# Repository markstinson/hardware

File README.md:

Internal OPL3 ISA 8 bits

version 1.0

With problems still unidentified. The schematic is based on texelec board Resound v1.1:

https://texelec.com/product/resound-opl3-4-channel-opl3-sound-card-8-bit-isa/

Symptoms:

The first start is always correct, it works and you can hear it perfectly, clear FM OPL3 sound ... but after approximately 2 minutes, it stops working. Normally a sleep period without connecting makes it work again, but there have been cases in which it stops working forever... it seems some kind of overload.

The ICs or components do not look hot, and the voltage tracks are not larger than the rest of the signals, this could be an error, however the width of the same should be sufficient for the mA demand of the ICs (I think) .

Another theory is that I do not use electrolytic 10uF capacitors as in the original design, they are 10uF without polarity, but in principle I think that should not affect the operation.

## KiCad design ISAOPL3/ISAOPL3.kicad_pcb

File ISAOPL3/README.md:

Internal OPL3 ISA 8 bits

version 1.0

With problems still unidentified. The schematic is based on texelec board Resound v1.1:

https://texelec.com/product/resound-opl3-4-channel-opl3-sound-card-8-bit-isa/

Symptoms:

The first start is always correct, it works and you can hear it perfectly, clear FM OPL3 sound ... but after approximately 2 minutes, it stops working. Normally a sleep period without connecting makes it work again, but there have been cases in which it stops working forever...  (that should be because component 74245 was not TTL, I've already put a TTL in it, now it always works after a rest period):

https://youtu.be/4GyFgOpV200

The ICs or components do not look hot, and the voltage tracks are not larger than the rest of the signals, this could be an error, however the width of the same should be sufficient for the mA demand of the ICs (I think) .

Another theory is that I do not use electrolytic 10uF capacitors as in the original design, they are 10uF without polarity, but in principle I think that should not affect the operation.

Is the width of the tracks? Is the position of the components? Is it the quality or type of components? Those're the questions.

Issue found:

The problem is in the 1uF WIMA capacitors. If after losing the sound I uncharge them with my finger, it works again!

There is a slight difference with the design of the Resound OPL, I have put the 1uJ63 on it and they use the 1uM63. I will try to determine that it is not any other design problem, in principle by replacing them with 1uF MLCCs.

Fix: 

Specifically the primary 1uF capacitors were left charged, I have solved this by adding a couple of resistors, I will post a demo video soon...

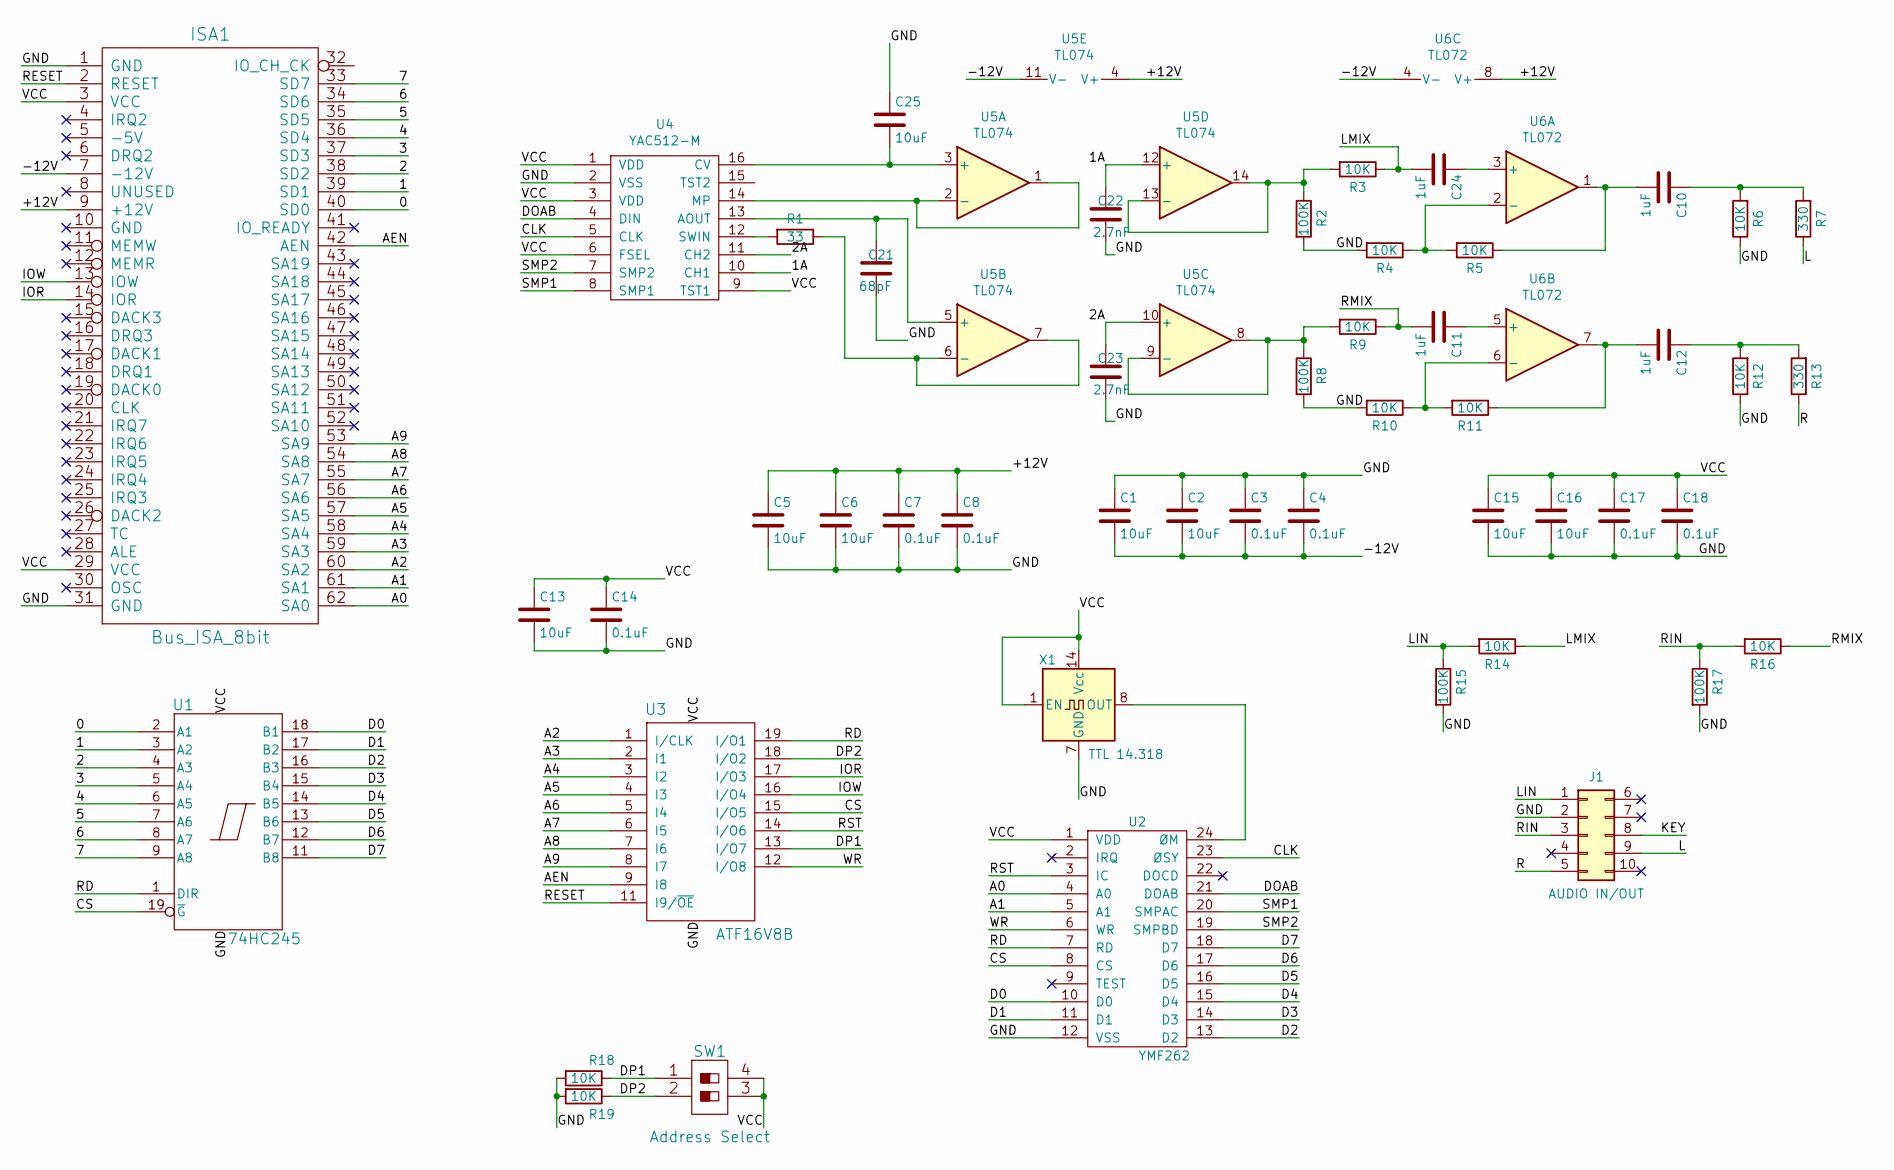
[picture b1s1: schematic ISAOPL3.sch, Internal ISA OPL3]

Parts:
C1, C2, C5, C6, C13, C15, C16, C25: 10uF; C_1206_3216Metric_Pad1.42x1.75mm_HandSolder
C3, C4, C7, C8, C14, C17, C18: 0.1uF; C_1206_3216Metric_Pad1.42x1.75mm_HandSolder
C10, C11, C12, C24: 1uF; C_Rect_L7.2mm_W7.2mm_P5.00mm_FKS2_FKP2_MKS2_MKP2
C21: 68pF; C_1206_3216Metric_Pad1.42x1.75mm_HandSolder
C22, C23: 2.7nF; C_1206_3216Metric_Pad1.42x1.75mm_HandSolder
ISA1: Bus_ISA_8bit; Conn_Edge_PCB_ISA8
J1: AUDIO IN/OUT; PinHeader_2x05_P2.54mm_Vertical_modificado
R1: 33; R_1206_3216Metric_Pad1.42x1.75mm_HandSolder
R2, R8, R15, R17: 100K; R_1206_3216Metric_Pad1.42x1.75mm_HandSolder
R3, R4, R5, R6, R9, R10, R11, R12, R14, R16, R18, R19: 10K; R_1206_3216Metric_Pad1.42x1.75mm_HandSolder
R7, R13: 330; R_1206_3216Metric_Pad1.42x1.75mm_HandSolder
SW1: Address Select; Switch_DIP_2_Positions
U1: 74HC245; IC_SOIC20_Wide
U2: YMF262; IC_SOIC24_Wide
U3: ATF16V8B; DIP-20_W7.62mm
U4: YAC512-M; IC_SOIC16_Wide
U5: TL074; IC_SOIC14_Narrow
U6: TL072; IC_SOIC8_Narrow
X1: TTL 14.318; Oscillator_DIP-14

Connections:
/0: ISA1.40 (SD0), U1.2 (A1)
/1: ISA1.39 (SD1), U1.3 (A2)
/1A: C22.1, U4.10 (CH1), U5.12 (+)
/2: ISA1.38 (SD2), U1.4 (A3)
/2A: C23.1, U4.11 (CH2), U5.10 (+)
/3: ISA1.37 (SD3), U1.5 (A4)
/4: ISA1.36 (SD4), U1.6 (A5)
/5: ISA1.35 (SD5), U1.7 (A6)
/6: ISA1.34 (SD6), U1.8 (A7)
/7: ISA1.33 (SD7), U1.9 (A8)
/+12V: C5.1, C6.1, C7.1, C8.1, ISA1.9 (+12V), U5.4 (V+), U6.8 (V+)
/-12V: C1.2, C2.2, C3.2, C4.2, ISA1.7 (-12V), U5.11 (V-), U6.4 (V-)
/A0: ISA1.62 (SA0), U2.4 (A0)
/A1: ISA1.61 (SA1), U2.5 (A1)
/A2: ISA1.60 (SA2), U3.1 (I/CLK)
/A3: ISA1.59 (SA3), U3.2 (I1)
/A4: ISA1.58 (SA4), U3.3 (I2)
/A5: ISA1.57 (SA5), U3.4 (I3)
/A6: ISA1.56 (SA6), U3.5 (I4)
/A7: ISA1.55 (SA7), U3.6 (I5)
/A8: ISA1.54 (SA8), U3.7 (I6)
/A9: ISA1.53 (SA9), U3.8 (I7)
/AEN: ISA1.42 (AEN), U3.9 (I8)
/CLK: U2.23 (ØSY), U4.5 (CLK)
/CS: U1.19 (~G), U2.8 (CS), U3.15 (I/O5)
/D0: U1.18 (B1), U2.10 (D0)
/D1: U1.17 (B2), U2.11 (D1)
/D2: U1.16 (B3), U2.13 (D2)
/D3: U1.15 (B4), U2.14 (D3)
/D4: U1.14 (B5), U2.15 (D4)
/D5: U1.13 (B6), U2.16 (D5)
/D6: U1.12 (B7), U2.17 (D6)
/D7: U1.11 (B8), U2.18 (D7)
/DOAB: U2.21 (DOAB), U4.4 (DIN)
/DP1: R18.1, SW1.1, U3.13 (I/O7)
/DP2: R19.1, SW1.2, U3.18 (I/O2)
/IOR: ISA1.14 (IOR), U3.17 (I/O3)
/IOW: ISA1.13 (IOW), U3.16 (I/O4)
/L: J1.9, R7.1
/LIN: J1.1, R14.2, R15.1
/LMIX: C24.2, R3.1, R14.1
/R: J1.5, R13.1
/RD: U1.1 (DIR), U2.7 (RD), U3.19 (I/O1)
/RESET: ISA1.2 (RESET), U3.11 (I9/~OE)
/RIN: J1.3, R16.2, R17.1
/RMIX: C11.2, R9.1, R16.1
/RST: U2.3 (IC), U3.14 (I/O6)
/SMP1: U2.20 (SMPAC), U4.8 (SMP1)
/SMP2: U2.19 (SMPBD), U4.7 (SMP2)
/WR: U2.6 (WR), U3.12 (I/O8)
GND: C1.1, C2.1, C3.1, C4.1, C5.2, C6.2, C7.2, C8.2, C13.2, C14.2, C15.2, C16.2, C17.2, C18.2, C21.2, C22.2, C23.2, C25.1, ISA1.1 (GND), ISA1.31 (GND), J1.2, R2.2, R4.2, R6.1, R8.2, R10.2, R12.1, R15.2, R17.2, R18.2, R19.2, U1.10 (GND), U2.12 (VSS), U3.10 (GND), U4.2 (VSS), X1.7 (GND)
unnamed: C10.1, R6.2, R7.2
unnamed: C10.2, R5.1, U6.1
unnamed: C11.1, U6.5 (+)
unnamed: C12.1, R12.2, R13.2
unnamed: C12.2, R11.1, U6.7
unnamed: C21.1, U4.13 (AOUT), U5.5 (+)
unnamed: C24.1, U6.3 (+)
unnamed: C25.2, U4.16 (CV), U5.3 (+)
unnamed: R1.1, U5.6 (-), U5.7
unnamed: R1.2, U4.12 (SWIN)
unnamed: R2.1, R3.2, U5.13 (-), U5.14
unnamed: R4.1, R5.2, U6.2 (-)
unnamed: R8.1, R9.2, U5.8, U5.9 (-)
unnamed: R10.1, R11.2, U6.6 (-)
unnamed: U2.24 (ØM), X1.8 (OUT)
unnamed: U4.14 (MP), U5.1, U5.2 (-)
VCC: C13.1, C14.1, C15.1, C16.1, C17.1, C18.1, ISA1.3 (VCC), ISA1.29 (VCC), SW1.3, SW1.4, U1.20 (VCC), U2.1 (VDD), U3.20 (VCC), U4.1 (VDD), U4.3 (VDD), U4.6 (FSEL), U4.9 (TST1), X1.1 (EN), X1.14 (Vcc)

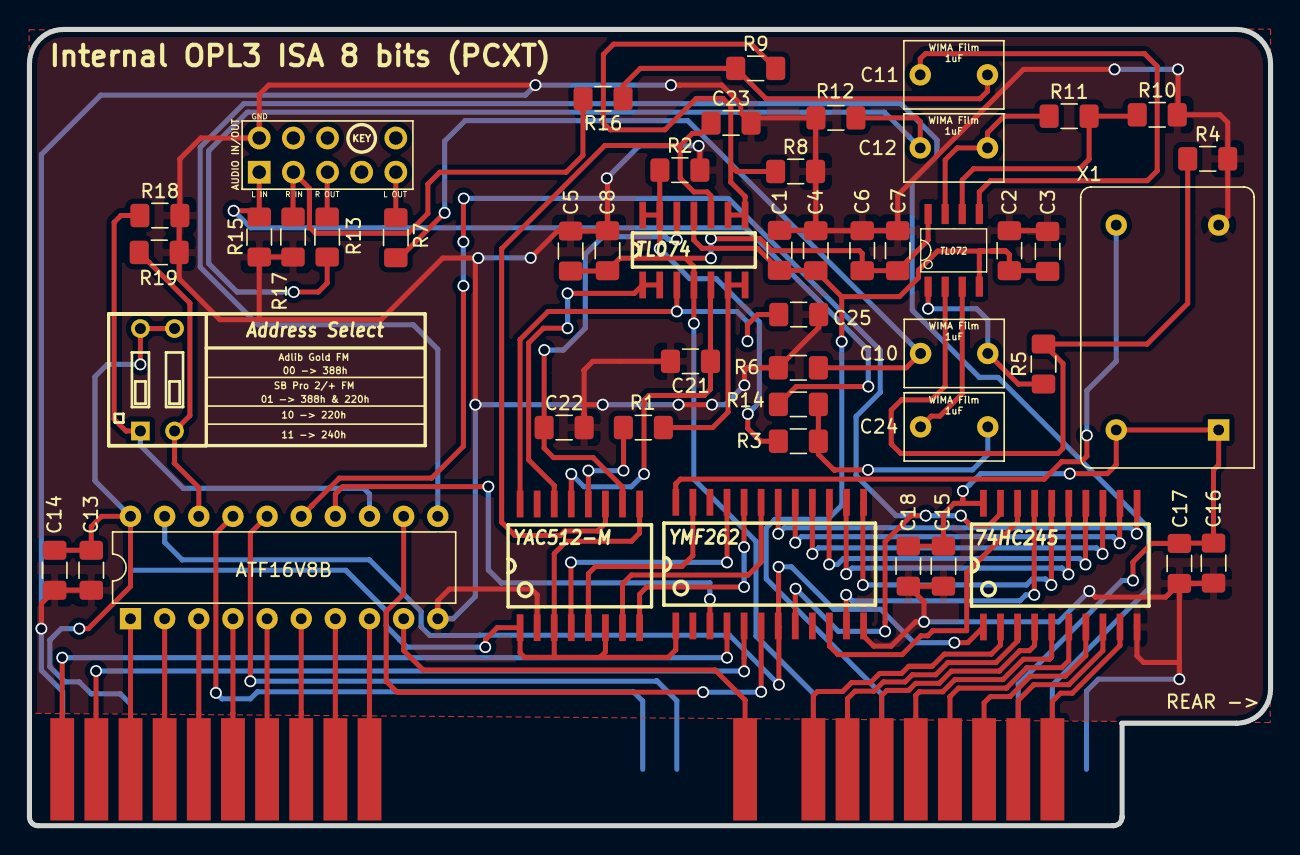
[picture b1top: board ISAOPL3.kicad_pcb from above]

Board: 2 copper layers, 92.3 x 59.2 mm, 51 parts (0 on the bottom side), 68 nets.

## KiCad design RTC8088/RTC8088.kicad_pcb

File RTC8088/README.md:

More information:

https://hackaday.io/project/168972-rtc-isa-8-bits-pcxt

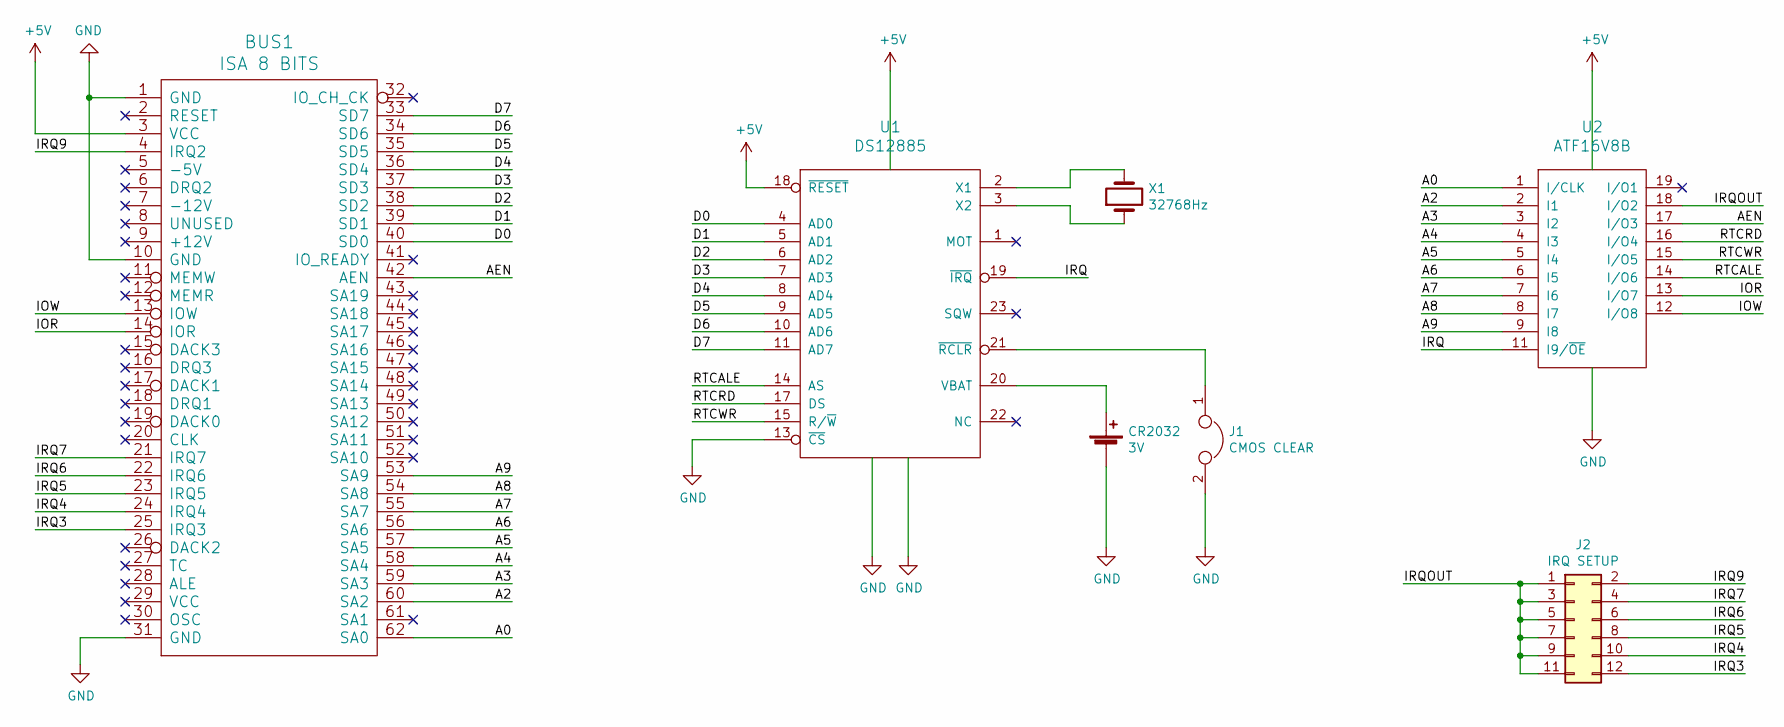
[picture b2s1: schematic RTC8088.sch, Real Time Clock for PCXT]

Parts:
BUS1: ISA 8 BITS; BUS_RTC8088
CR2032: 3V; Battery_Holder_CR2032_Mouser_122-2520-GR
J1: CMOS CLEAR; Conn_Pin_Header_2x1_2.54mm_NoKey
J2: IRQ SETUP; PinHeader_2x06_P2.54mm_Vertical
U1: DS12885; IC_DIP24_600
U2: ATF16V8B; IC_DIP20_300
X1: 32768Hz; Crystal_32K_Vert

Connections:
+5V: BUS1.3 (VCC), U1.18 (~RESET), U1.24 (VCC), U2.20 (VCC)
/A0: BUS1.62 (SA0), U2.1 (I/CLK)
/A2: BUS1.60 (SA2), U2.2 (I1)
/A3: BUS1.59 (SA3), U2.3 (I2)
/A4: BUS1.58 (SA4), U2.4 (I3)
/A5: BUS1.57 (SA5), U2.5 (I4)
/A6: BUS1.56 (SA6), U2.6 (I5)
/A7: BUS1.55 (SA7), U2.7 (I6)
/A8: BUS1.54 (SA8), U2.8 (I7)
/A9: BUS1.53 (SA9), U2.9 (I8)
/AEN: BUS1.42 (AEN), U2.17 (I/O3)
/D0: BUS1.40 (SD0), U1.4 (AD0)
/D1: BUS1.39 (SD1), U1.5 (AD1)
/D2: BUS1.38 (SD2), U1.6 (AD2)
/D3: BUS1.37 (SD3), U1.7 (AD3)
/D4: BUS1.36 (SD4), U1.8 (AD4)
/D5: BUS1.35 (SD5), U1.9 (AD5)
/D6: BUS1.34 (SD6), U1.10 (AD6)
/D7: BUS1.33 (SD7), U1.11 (AD7)
/IOR: BUS1.14 (IOR), U2.13 (I/O7)
/IOW: BUS1.13 (IOW), U2.12 (I/O8)
/IRQ: U1.19 (~IRQ), U2.11 (I9/~OE)
/IRQ3: BUS1.25 (IRQ3), J2.12
/IRQ4: BUS1.24 (IRQ4), J2.10
/IRQ5: BUS1.23 (IRQ5), J2.8
/IRQ6: BUS1.22 (IRQ6), J2.6
/IRQ7: BUS1.21 (IRQ7), J2.4
/IRQ9: BUS1.4 (IRQ2), J2.2
/IRQOUT: J2.1, J2.3, J2.5, J2.7, J2.9, J2.11, U2.18 (I/O2)
/RTCALE: U1.14 (AS), U2.14 (I/O6)
/RTCRD: U1.17 (DS), U2.16 (I/O4)
/RTCWR: U1.15 (R/~W~), U2.15 (I/O5)
GND: BUS1.1 (GND), BUS1.10 (GND), BUS1.31 (GND), CR2032.2 (-), J1.2, U1.12 (GND), U1.13 (~CS), U1.16 (GND), U2.10 (GND)
unnamed: CR2032.1 (+), U1.20 (VBAT)
unnamed: J1.1, U1.21 (~RCLR)
unnamed: U1.2 (X1), X1.2
unnamed: U1.3 (X2), X1.1

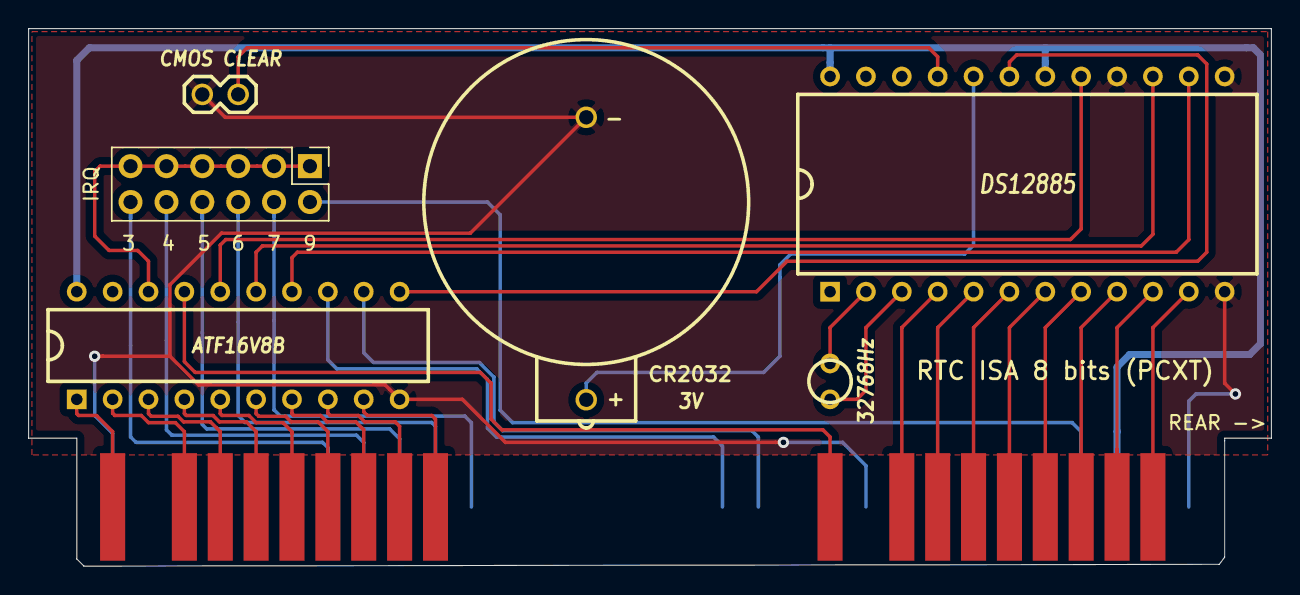
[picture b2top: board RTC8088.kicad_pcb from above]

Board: 2 copper layers, 88.0 x 38.1 mm, 7 parts (0 on the bottom side), 37 nets.

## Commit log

2019-07-02 Disclaimer
2019-10-12 Update to version with diodes
2019-12-21 RTC8088
    RTC8088 Kicad project, gerbers and SPLD files.
2020-01-02 Delete MonochromeVGA.brd
    It has a issue in the design of the board, pending correction ... I add the right gerbers.
2020-01-02 I add gerbers
2020-07-09 v1.2
    Diode is added between GND and VBAT for correct detection of absence of battery.
